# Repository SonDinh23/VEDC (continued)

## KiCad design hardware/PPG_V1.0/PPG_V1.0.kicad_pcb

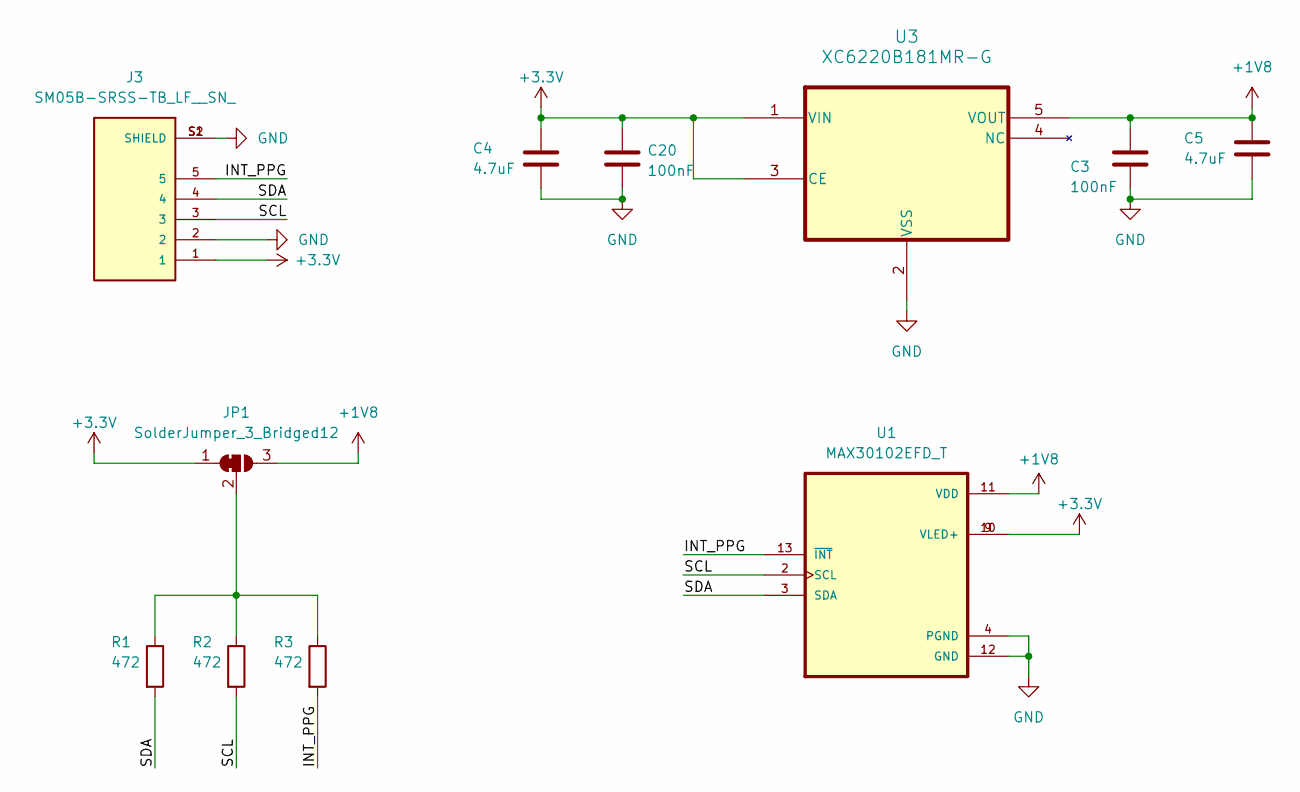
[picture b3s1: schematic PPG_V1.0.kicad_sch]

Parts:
C3, C20: 100nF; C_0402_1005Metric
C4, C5: 4.7uF; C_0402_1005Metric
J3: SM05B-SRSS-TB_LF__SN_; JST_SM05B-SRSS-TB_LF__SN_
JP1: SolderJumper_3_Bridged12; SolderJumper-3_P1.3mm_Bridged12_RoundedPad1.0x1.5mm_NumberL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
R1, R2, R3: 472; C_0402_1005Metric
U1: MAX30102EFD_T; XDCR_MAX30101EFD_
U3: XC6220B181MR-G; SOT-25_TOR

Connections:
+1V8: C3.1, C5.1, JP1.3 (B), U1.11 (VDD), U3.5 (VOUT)
+3.3V: C4.1, C20.1, J3.1, JP1.1 (A), U1.9 (VLED+), U1.10 (VLED+), U3.1 (VIN), U3.3 (CE)
/INT_PPG: J3.5, R3.2, U1.13 (~INT)
/SCL: J3.3, R2.2, U1.2 (SCL)
/SDA: J3.4, R1.2, U1.3 (SDA)
GND: C3.2, C4.2, C5.2, C20.2, J3.2, J3.S1 (SHIELD), J3.S2 (SHIELD), U1.4 (PGND), U1.12 (GND), U3.2 (VSS)
unnamed: JP1.2 (C), R1.1, R2.1, R3.1

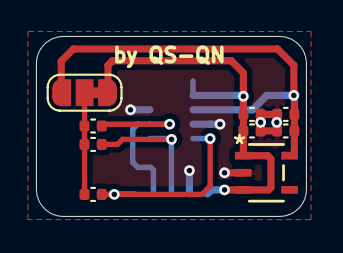
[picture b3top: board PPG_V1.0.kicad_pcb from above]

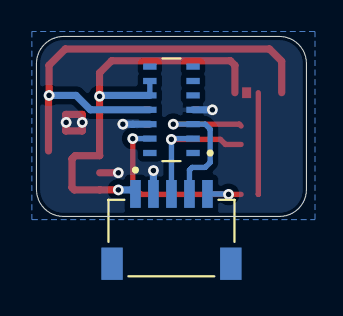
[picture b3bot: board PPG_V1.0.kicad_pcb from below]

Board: 2 copper layers, 15.0 x 10.0 mm, 11 parts (2 on the bottom side), 7 nets.

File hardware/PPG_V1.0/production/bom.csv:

Designator,Footprint,Quantity,Value,LCSC Part #
"C20, C3",0402,2,100nF,
"C4, C5",0402,2,4.7uF,
J3,JST_SM05B-SRSS-TB_LF__SN_,1,SM05B-SRSS-TB_LF__SN_,
"R1, R2, R3",0402,3,472,
U1,XDCR_MAX30101EFD_,1,MAX30102EFD_T,
U3,SOT-25_TOR,1,XC6220B181MR-G,

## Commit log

2025-12-01 feature: Adjust the directory management system
2025-12-03 feature: additional drawing hardware
2025-12-03 feature: Change and add information to the hardware Readme file
2025-12-04 feature: additional firmware | fix: added some content to the readme file
2025-12-06 feature: additional App
2025-12-09 feature: add firebase, add send data email, add 3d imu simulation, optime FW
2025-12-12 fix: screen information about firebase get data
